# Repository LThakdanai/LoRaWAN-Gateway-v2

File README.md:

# LoRaWAN Gateway
---------------------------------------------------------------------------------------- 
This github is part of LoRaWAN Gateway Thesis as Institute of Field Robotics (FIBO)
## Schamatic Design
In this part please check on file name: output.pdf

## Each Layer of PCB
First Layer:

Second Layer:

Third Layer:

Button Layer:

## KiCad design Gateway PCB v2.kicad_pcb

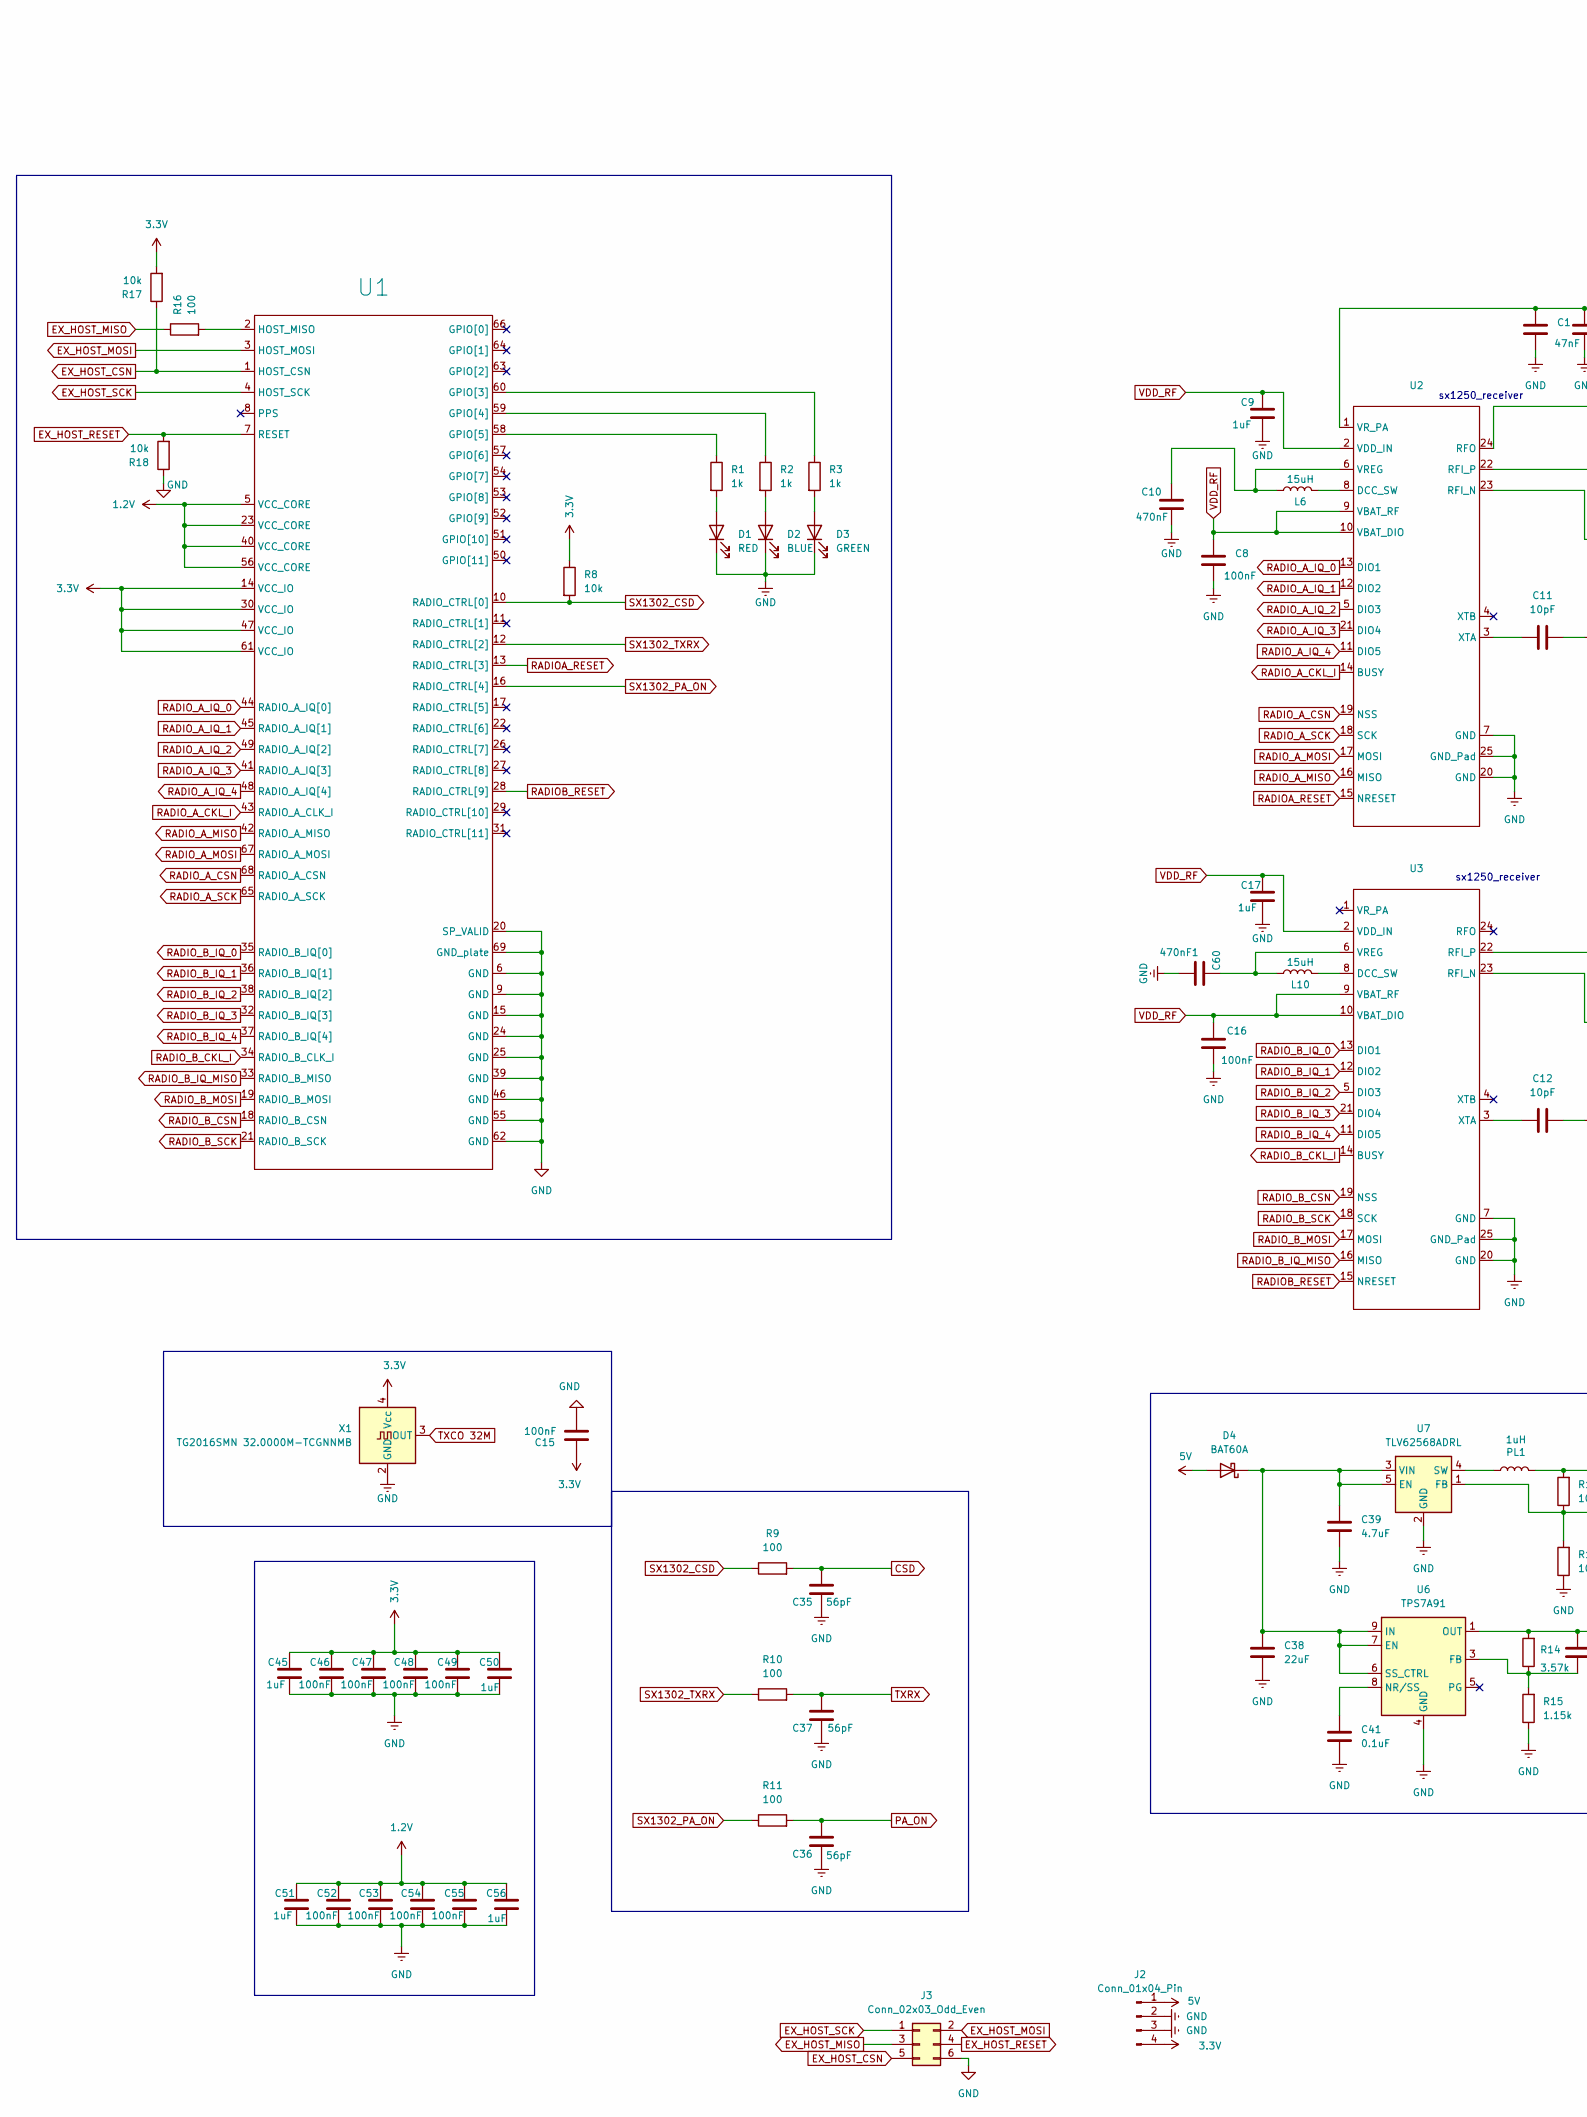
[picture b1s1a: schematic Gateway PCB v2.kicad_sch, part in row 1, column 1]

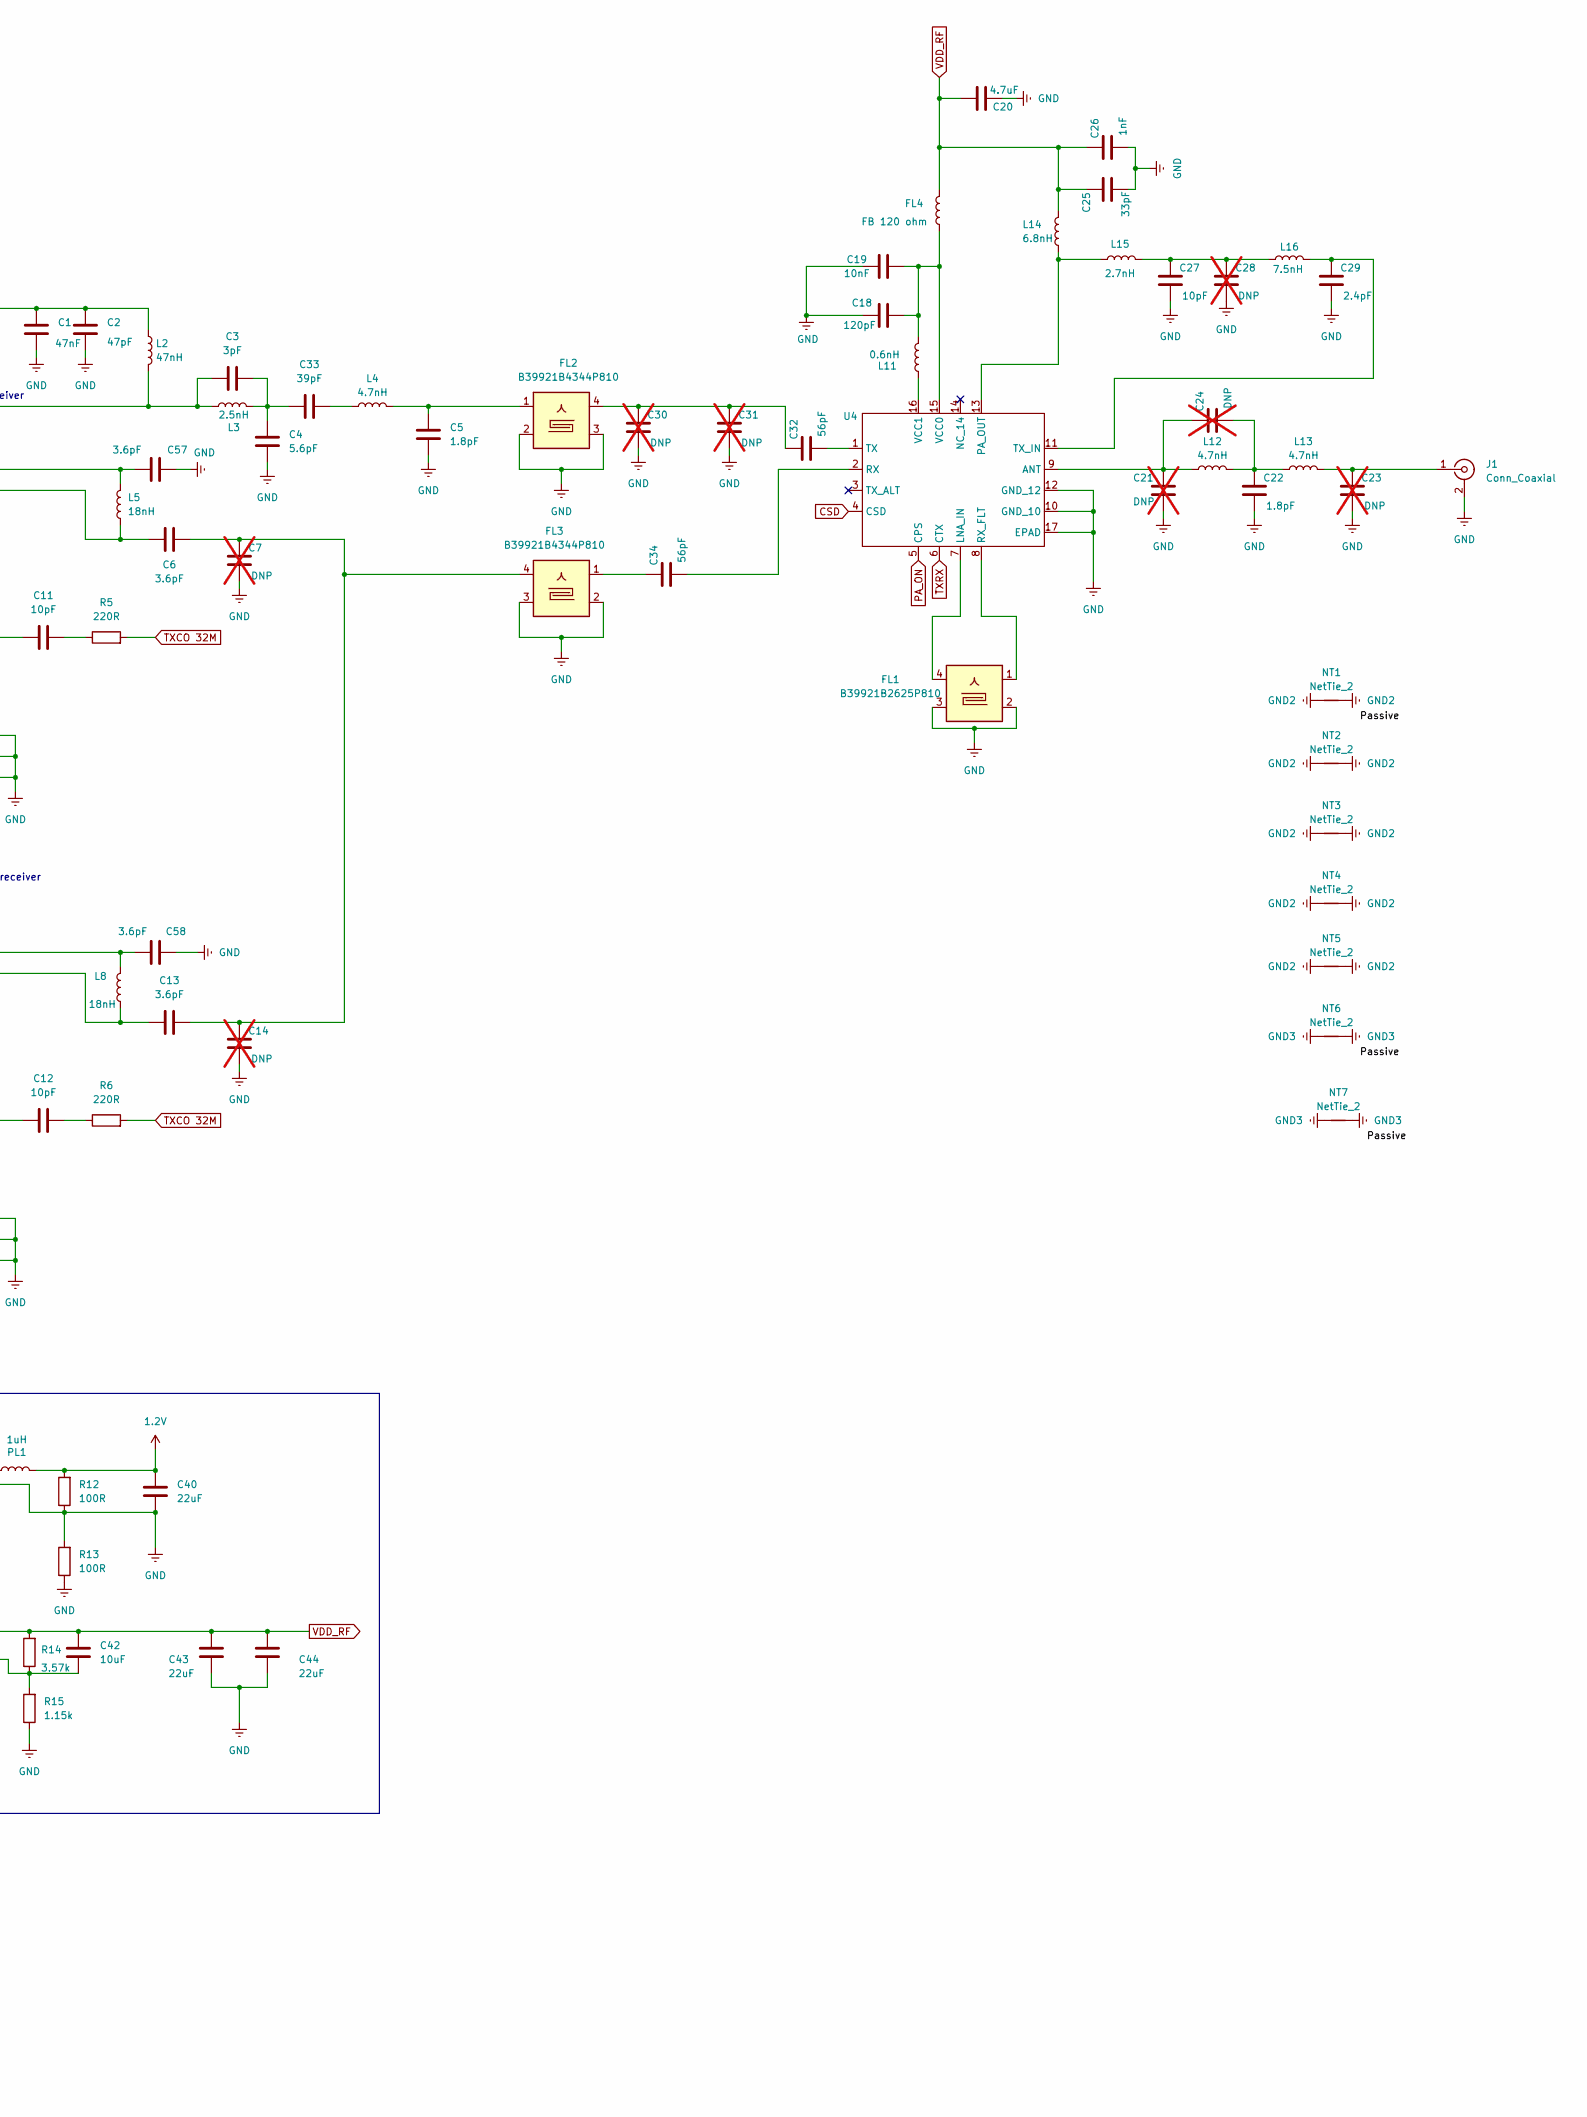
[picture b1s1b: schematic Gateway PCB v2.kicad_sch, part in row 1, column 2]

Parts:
C1: 47nF; C_0402_1005Metric_Pad0.74x0.62mm_HandSolder
C2: 47pF; C_0402_1005Metric_Pad0.74x0.62mm_HandSolder
C3: 3pF; C_0402_1005Metric_Pad0.74x0.62mm_HandSolder
C4: 5.6pF; C_0402_1005Metric_Pad0.74x0.62mm_HandSolder
C5, C22: 1.8pF; C_0402_1005Metric_Pad0.74x0.62mm_HandSolder
C6, C13, C57, C58: 3.6pF; C_0402_1005Metric_Pad0.74x0.62mm_HandSolder
C7, C14, C21, C23, C24, C28, C30, C31: DNP; C_0402_1005Metric_Pad0.74x0.62mm_HandSolder; not fitted
C8, C15, C16, C46, C47, C48, C49, C52, C53, C54, C55: 100nF; C_0402_1005Metric_Pad0.74x0.62mm_HandSolder
C9, C17, C45, C50, C51, C56: 1uF; C_0402_1005Metric_Pad0.74x0.62mm_HandSolder
C10: 470nF; C_0402_1005Metric_Pad0.74x0.62mm_HandSolder
C11, C12, C27: 10pF; C_0402_1005Metric_Pad0.74x0.62mm_HandSolder
C18: 120pF; C_0402_1005Metric_Pad0.74x0.62mm_HandSolder
C19: 10nF; C_0402_1005Metric_Pad0.74x0.62mm_HandSolder
C20: 4.7uF; C_0402_1005Metric_Pad0.74x0.62mm_HandSolder
C25: 33pF; C_0402_1005Metric_Pad0.74x0.62mm_HandSolder
C26: 1nF; C_0402_1005Metric_Pad0.74x0.62mm_HandSolder
C29: 2.4pF; C_0402_1005Metric_Pad0.74x0.62mm_HandSolder
C32, C34, C35, C36, C37: 56pF; C_0402_1005Metric_Pad0.74x0.62mm_HandSolder
C33: 39pF; C_0402_1005Metric_Pad0.74x0.62mm_HandSolder
C38, C40: 22uF; C_0603_1608Metric_Pad1.08x0.95mm_HandSolder
C39: 4.7uF; C_0603_1608Metric_Pad1.08x0.95mm_HandSolder
C41: 0.1uF; C_0402_1005Metric_Pad0.74x0.62mm_HandSolder
C42: 10uF; C_0402_1005Metric_Pad0.74x0.62mm_HandSolder
C43, C44: 22uF; C_0402_1005Metric_Pad0.74x0.62mm_HandSolder
C60: 470nF1; C_0402_1005Metric_Pad0.74x0.62mm_HandSolder
D1: RED; LED_0603_1608Metric_Pad1.05x0.95mm_HandSolder
D2: BLUE; LED_0603_1608Metric_Pad1.05x0.95mm_HandSolder
D3: GREEN; LED_0603_1608Metric_Pad1.05x0.95mm_HandSolder
D4: BAT60A; D_SOD-323
FL1: B39921B2625P810; Filter_1411-5_1.4x1.1mm
FL2, FL3: B39921B4344P810; Filter_1411-5_1.4x1.1mm
FL4: FB 120 ohm; L_0402_1005Metric
J1: Conn_Coaxial; SMA_BAT_Wireless_BWSMA-KWE-Z001
J2: Conn_01x04_Pin; PinHeader_1x04_P2.54mm_Vertical
J3: Conn_02x03_Odd_Even; PinHeader_1x06_P2.54mm_Vertical
L2: 47nH; L_0402_1005Metric_Pad0.77x0.64mm_HandSolder
L3: 2.5nH; L_0402_1005Metric_Pad0.77x0.64mm_HandSolder
L4, L12, L13: 4.7nH; L_0402_1005Metric_Pad0.77x0.64mm_HandSolder
L5, L8: 18nH; L_0402_1005Metric_Pad0.77x0.64mm_HandSolder
L6, L10: 15uH; L_0805_2012Metric_Pad1.05x1.20mm_HandSolder
L11: 0.6nH; L_0402_1005Metric_Pad0.77x0.64mm_HandSolder
L14: 6.8nH; L_0402_1005Metric_Pad0.77x0.64mm_HandSolder
L15: 2.7nH; L_0402_1005Metric_Pad0.77x0.64mm_HandSolder
L16: 7.5nH; L_0402_1005Metric_Pad0.77x0.64mm_HandSolder
NT1, NT2, NT3, NT4, NT5, NT6, NT7: NetTie_2; NetTie-2_SMD_Pad0.5mm
PL1: 1uH; L_1008_2520Metric_Pad1.43x2.20mm_HandSolder
R1, R2, R3: 1k; R_0402_1005Metric_Pad0.72x0.64mm_HandSolder
R5, R6: 220R; R_0402_1005Metric_Pad0.72x0.64mm_HandSolder
R8, R17, R18: 10k; R_0402_1005Metric_Pad0.72x0.64mm_HandSolder
R9, R10, R11, R16: 100; R_0402_1005Metric_Pad0.72x0.64mm_HandSolder
R12, R13: 100R; R_0402_1005Metric_Pad0.72x0.64mm_HandSolder
R14: 3.57k; R_0402_1005Metric_Pad0.72x0.64mm_HandSolder
R15: 1.15k; R_0402_1005Metric_Pad0.72x0.64mm_HandSolder
U1: SX1302
U2, U3: HVQFN-24-1EP_4x4mm_P0.5mm_EP2.5x2.5mm
U4: QFN-16-1EP_3x3mm_P0.5mm_EP1.75x1.75mm
U6: TPS7A91; Texas_S-PDSO-N10_EP1.2x2mm
U7: TLV62568ADRL; SOT-563
X1: TG2016SMN 32.0000M-TCGNNMB; Oscillator_SMD_SeikoEpson_TG2520SMN-xxx-xxxxxx-4Pin_2.5x2.0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

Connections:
1.2V: C40.2, C51.1, C52.1, C53.1, C54.1, C55.1, C56.1, PL1.2, R12.2, U1.5 (VCC_CORE), U1.23 (VCC_CORE), U1.40 (VCC_CORE), U1.56 (VCC_CORE)
3.3V: C15.1, C45.1, C46.1, C47.1, C48.1, C49.1, C50.1, J2.4, R8.1, R17.2, U1.14 (VCC_IO), U1.30 (VCC_IO), U1.47 (VCC_IO), U1.61 (VCC_IO), X1.4 (Vcc)
5V: D4.2 (A), J2.1
CSD: C35.2, R9.2, U4.4 (CSD); also elsewhere on the board
EX_HOST_CSN: J3.5, R17.1, U1.1 (HOST_CSN)
EX_HOST_MISO: J3.3, R16.1
EX_HOST_MOSI: J3.2, U1.3 (HOST_MOSI)
EX_HOST_RESET: J3.4, R18.2, U1.7 (RESET)
EX_HOST_SCK: J3.1, U1.4 (HOST_SCK)
GND2: NT1.1, NT1.2, NT2.1, NT2.2, NT3.1, NT3.2, NT4.1, NT4.2, NT5.1, NT5.2
unnamed: C3.2, C4.1, C33.1, L3.2
unnamed: C5.1, FL2.1, L4.2
unnamed: C11.2, R5.1
unnamed: C12.2, R6.1
unnamed: C6.2, C7.1, C13.2, C14.1, FL3.4
unnamed: C22.1, C24.2, L12.2, L13.1
unnamed: C27.1, C28.1, L15.2, L16.1
unnamed: C30.1, C31.1, C32.1, FL2.4
unnamed: C33.2, L4.1
unnamed: C34.1, FL3.1
unnamed: D1.2 (A), R1.2
unnamed: D2.2 (A), R2.2
unnamed: D3.2 (A), R3.2
unnamed: C38.2, C39.2, D4.1 (K), U6.6 (SS_CTRL), U6.7 (EN), U6.9 (IN), U6.10 (IN), U7.3 (VIN), U7.5 (EN)
unnamed: C23.1, J1.1 (In), L13.2
unnamed: NT6.1, NT6.2, NT7.1, NT7.2
unnamed: R3.1, U1.60 (GPIO[3])
unnamed: R2.1, U1.59 (GPIO[4])
unnamed: R1.1, U1.58 (GPIO[5])
unnamed: R16.2, U1.2 (HOST_MISO)
unnamed: L6.2, U2.8 (DCC_SW)
unnamed: C6.1, L5.1, U2.23 (RFI_N)
unnamed: C57.2, L5.2, U2.22 (RFI_P)
unnamed: C3.1, L2.2, L3.1, U2.24 (RFO)
unnamed: C10.1, L6.1, U2.6 (VREG)
unnamed: C1.1, C2.1, L2.1, U2.1 (VR_PA)
unnamed: C11.1, U2.3 (XTA)
unnamed: L10.2, U3.8 (DCC_SW)
unnamed: C13.1, L8.1, U3.23 (RFI_N)
unnamed: C58.2, L8.2, U3.22 (RFI_P)
unnamed: C60.1, L10.1, U3.6 (VREG)
unnamed: C12.1, U3.3 (XTA)
unnamed: C21.1, C24.1, L12.1, U4.9 (ANT)
unnamed: FL1.4, U4.7 (LNA_IN)
unnamed: L14.1, L15.1, U4.13 (PA_OUT)
unnamed: C34.2, U4.2 (RX)
unnamed: FL1.1, U4.8 (RX_FLT)
unnamed: C32.2, U4.1 (TX)
unnamed: C29.1, L16.2, U4.11 (TX_IN)
unnamed: C18.1, C19.1, FL4.1, L11.2, U4.15 (VCC0)
unnamed: L11.1, U4.16 (VCC1)
unnamed: C42.1, R14.1, R15.2, U6.3 (FB)
unnamed: C41.2, U6.8 (NR/SS)
unnamed: PL1.1, U7.4 (SW)
PA_ON: C36.2, R11.2, U4.5 (CPS); also elsewhere on the board
RADIOA_RESET: U1.13 (RADIO_CTRL[3]), U2.15 (NRESET)
RADIOB_RESET: U1.28 (RADIO_CTRL[9]), U3.15 (NRESET)
RADIO_A_CKL_I: U1.43 (RADIO_A_CLK_I), U2.14 (BUSY)
RADIO_A_CSN: U1.68 (RADIO_A_CSN), U2.19 (NSS)
RADIO_A_IQ_0: U1.44 (RADIO_A_IQ[0]), U2.13 (DIO1)
RADIO_A_IQ_1: U1.45 (RADIO_A_IQ[1]), U2.12 (DIO2)
RADIO_A_IQ_2: U1.49 (RADIO_A_IQ[2]), U2.5 (DIO3)
RADIO_A_IQ_3: U1.41 (RADIO_A_IQ[3]), U2.21 (DIO4)
RADIO_A_IQ_4: U1.48 (RADIO_A_IQ[4]), U2.11 (DIO5)
RADIO_A_MISO: U1.42 (RADIO_A_MISO), U2.16 (MISO)
RADIO_A_MOSI: U1.67 (RADIO_A_MOSI), U2.17 (MOSI)
RADIO_A_SCK: U1.65 (RADIO_A_SCK), U2.18 (SCK)
RADIO_B_CKL_I: U1.34 (RADIO_B_CLK_I), U3.14 (BUSY)
RADIO_B_CSN: U1.18 (RADIO_B_CSN), U3.19 (NSS)
RADIO_B_IQ_0: U1.35 (RADIO_B_IQ[0]), U3.13 (DIO1)
RADIO_B_IQ_1: U1.36 (RADIO_B_IQ[1]), U3.12 (DIO2)
RADIO_B_IQ_2: U1.38 (RADIO_B_IQ[2]), U3.5 (DIO3)
RADIO_B_IQ_3: U1.32 (RADIO_B_IQ[3]), U3.21 (DIO4)
RADIO_B_IQ_4: U1.37 (RADIO_B_IQ[4]), U3.11 (DIO5)
RADIO_B_IQ_MISO: U1.33 (RADIO_B_MISO), U3.16 (MISO)
RADIO_B_MOSI: U1.19 (RADIO_B_MOSI), U3.17 (MOSI)
RADIO_B_SCK: U1.21 (RADIO_B_SCK), U3.18 (SCK)
SX1302_CSD: R8.2, R9.1, U1.10 (RADIO_CTRL[0])
SX1302_PA_ON: R11.1, U1.16 (RADIO_CTRL[4])
SX1302_TXRX: R10.1, U1.12 (RADIO_CTRL[2])
TXCO 32M: R5.2, R6.2, X1.3 (OUT)
TXRX: C37.2, R10.2, U4.6 (CTX); also elsewhere on the board
VDD_RF: C8.1, C9.1, C16.1, C17.1, C20.1, C25.1, C26.1, C42.2, C43.2, C44.2, FL4.2, L14.2, R14.2, U2.2 (VDD_IN), U2.9 (VBAT_RF), U2.10 (VBAT_DIO), U3.2 (VDD_IN), U3.9 (VBAT_RF), U3.10 (VBAT_DIO), U6.1 (OUT), U6.2 (OUT)

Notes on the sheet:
sx1250_receiver

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
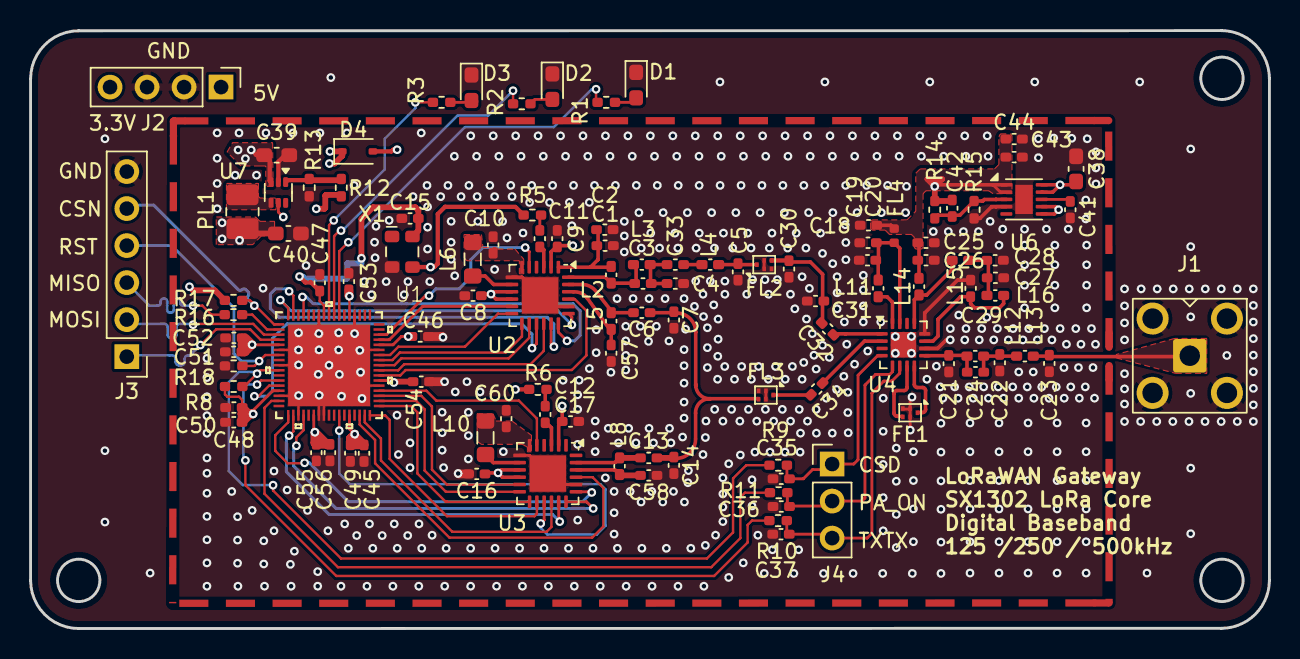
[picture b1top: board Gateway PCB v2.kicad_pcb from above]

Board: 4 copper layers, 85.0 x 41.0 mm, 113 parts (0 on the bottom side), 84 nets.

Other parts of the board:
J4: Conn_01x03_Pin; PinHeader_1x03_P2.54mm_Vertical

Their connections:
CSD: J4.1; also elsewhere on the board
PA_ON: J4.2; also elsewhere on the board
TXRX: J4.3; also elsewhere on the board

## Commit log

2025-03-20 first state
2025-03-23 re route sky
2025-03-27 Fail Save
2025-03-30 Increse size
2025-04-04 Fix Ubuntu
2025-04-14 Fail Save 2
2025-04-17 Fail Save 3
2025-04-19 Fail Save 4
2025-04-20 Success
2025-06-12 Fix Repo
2025-06-12 img add
2025-06-12 rename image
2025-06-12 read

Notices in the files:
parts and their libraries:
Copyright 2016 Accelerated Designs. All rights reserved.
